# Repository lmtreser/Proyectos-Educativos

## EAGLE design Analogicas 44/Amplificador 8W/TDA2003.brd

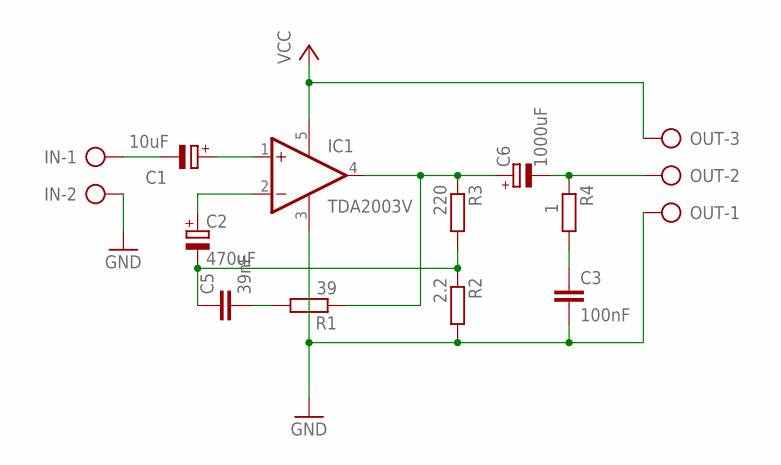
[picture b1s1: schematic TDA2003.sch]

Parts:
C1: 10uF; E2,5-6
C2: 470uF; E5-10,5
C3: 100nF; C025-025X050
C5: 39nF; C025-025X050
C6: 1000uF; E5-13
IC1: TDA2003V; CB360
IN: AK500/2-H
OUT: AK500/3-H
R1: 39; 0207/10
R2: 2.2; 0207/10
R3: 220; 0207/10
R4: 1; 0207/10

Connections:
GND: C3.2, IC1.3 (GND), IN.2, OUT.1, R2.2
unnamed: C1.+, IC1.1 (+IN)
unnamed: C1.-, IN.1
unnamed: C6.+, IC1.4 (OUT), R1.1, R3.1
unnamed: C6.-, OUT.2, R4.1
unnamed: C2.-, C5.1, R2.1, R3.2
unnamed: C3.1, R4.2
unnamed: C2.+, IC1.2 (-IN)
unnamed: C5.2, R1.2
VCC: IC1.5 (V+), OUT.3

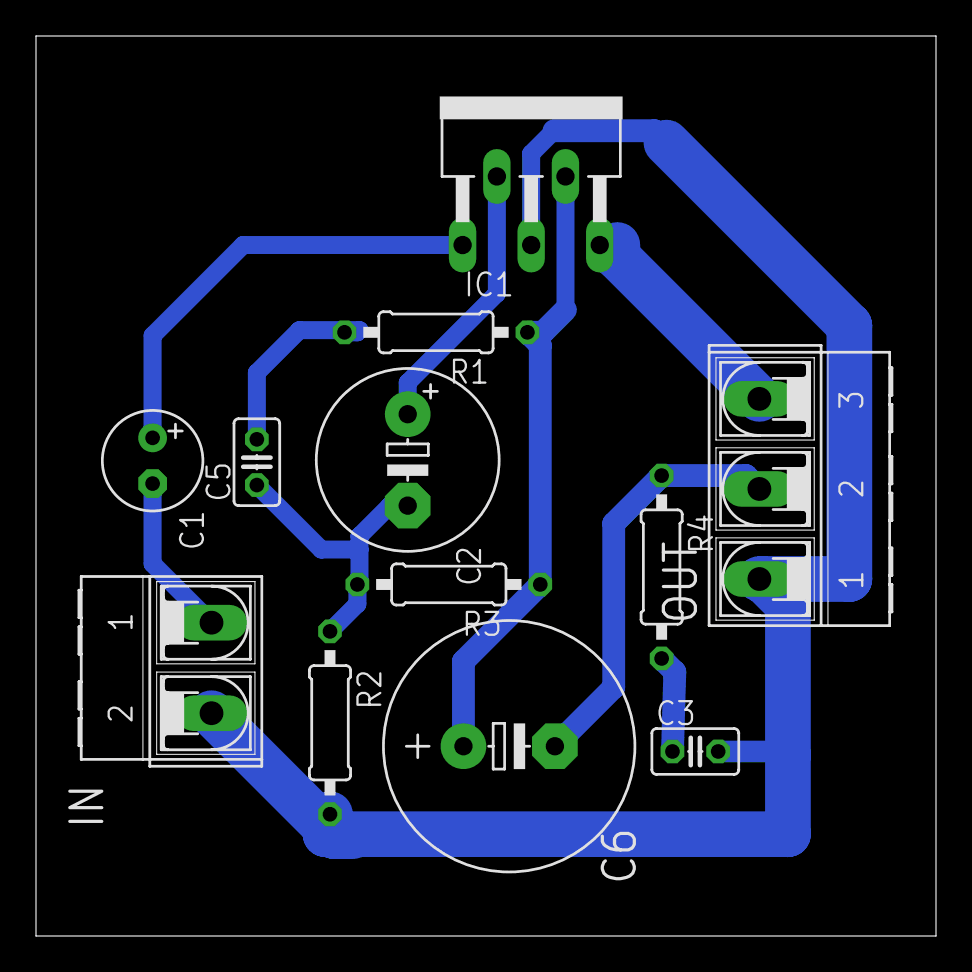
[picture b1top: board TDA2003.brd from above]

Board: 2 copper layers, 50.0 x 50.0 mm, 12 parts (0 on the bottom side), 10 nets.

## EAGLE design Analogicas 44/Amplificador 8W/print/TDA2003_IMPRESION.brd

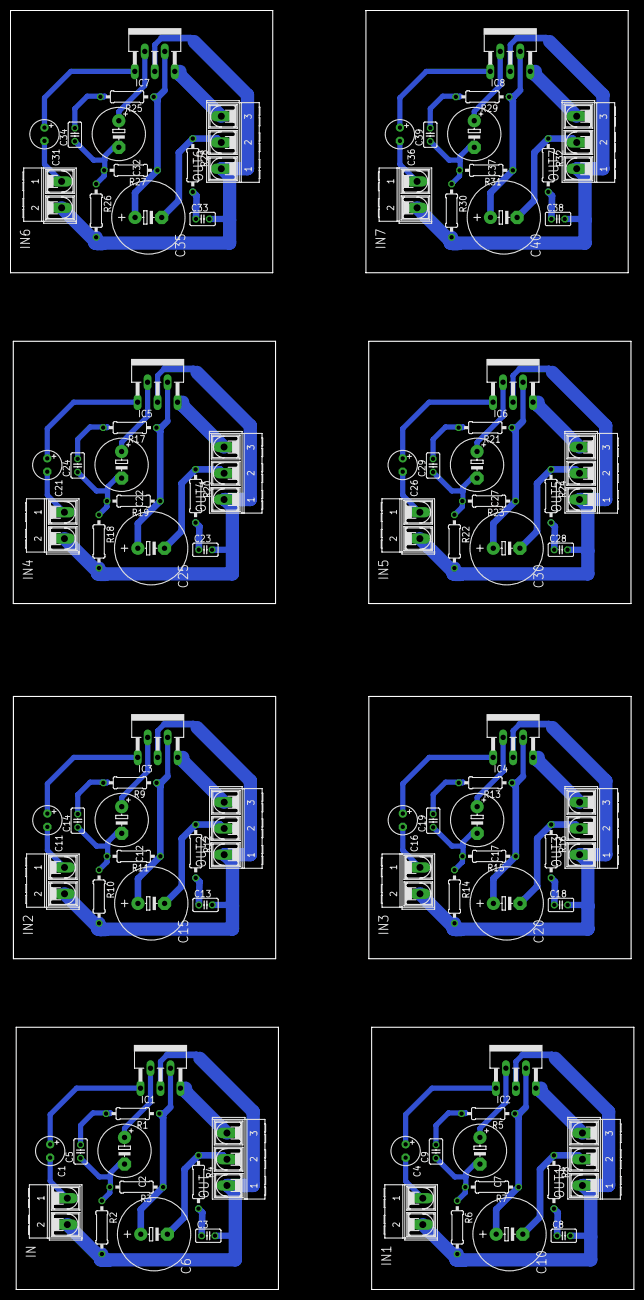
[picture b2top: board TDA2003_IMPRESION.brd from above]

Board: 2 copper layers, 118.9 x 243.9 mm, 96 parts (0 on the bottom side), 80 nets.

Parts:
C1, C4, C11, C16, C21, C26, C31, C36: 10uF; E2,5-6
C2, C7, C12, C17, C22, C27, C32, C37: 470uF; E5-10,5
C3, C8, C13, C18, C23, C28, C33, C38: 100nF; C025-025X050
C5, C9, C14, C19, C24, C29, C34, C39: 39nF; C025-025X050
C6, C10, C15, C20, C25, C30, C35, C40: 1000uF; E5-13
IC1, IC2, IC3, IC4, IC5, IC6, IC7, IC8: TDA2003V; CB360
IN, IN1, IN2, IN3, IN4, IN5, IN6, IN7: AK500/2-H
OUT, OUT1, OUT2, OUT3, OUT4, OUT5, OUT6, OUT7: AK500/3-H
R1, R5, R9, R13, R17, R21, R25, R29: 39; 0207/10
R2, R6, R10, R14, R18, R22, R26, R30: 2.2; 0207/10
R3, R7, R11, R15, R19, R23, R27, R31: 220; 0207/10
R4, R8, R12, R16, R20, R24, R28, R32: 1; 0207/10

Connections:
GND: C3.2, IC1.3, IN.2, OUT.1, R2.2
GND1: C8.2, IC2.3, IN1.2, OUT1.1, R6.2
GND2: C13.2, IC3.3, IN2.2, OUT2.1, R10.2
GND3: C18.2, IC4.3, IN3.2, OUT3.1, R14.2
GND4: C23.2, IC5.3, IN4.2, OUT4.1, R18.2
GND5: C28.2, IC6.3, IN5.2, OUT5.1, R22.2
GND6: C33.2, IC7.3, IN6.2, OUT6.1, R26.2
GND7: C38.2, IC8.3, IN7.2, OUT7.1, R30.2
unnamed: C1.+, IC1.1
unnamed: C1.-, IN.1
unnamed: C6.+, IC1.4, R1.1, R3.1
unnamed: C6.-, OUT.2, R4.1
unnamed: C2.-, C5.1, R2.1, R3.2
unnamed: C3.1, R4.2
unnamed: C2.+, IC1.2
unnamed: C5.2, R1.2
unnamed: C4.+, IC2.1
unnamed: C4.-, IN1.1
unnamed: C10.+, IC2.4, R5.1, R7.1
unnamed: C10.-, OUT1.2, R8.1
unnamed: C7.-, C9.1, R6.1, R7.2
unnamed: C8.1, R8.2
unnamed: C7.+, IC2.2
unnamed: C9.2, R5.2
unnamed: C11.+, IC3.1
unnamed: C11.-, IN2.1
unnamed: C15.+, IC3.4, R9.1, R11.1
unnamed: C15.-, OUT2.2, R12.1
unnamed: C12.-, C14.1, R10.1, R11.2
unnamed: C13.1, R12.2
unnamed: C12.+, IC3.2
unnamed: C14.2, R9.2
unnamed: C16.+, IC4.1
unnamed: C16.-, IN3.1
unnamed: C20.+, IC4.4, R13.1, R15.1
unnamed: C20.-, OUT3.2, R16.1
unnamed: C17.-, C19.1, R14.1, R15.2
unnamed: C18.1, R16.2
unnamed: C17.+, IC4.2
unnamed: C19.2, R13.2
unnamed: C21.+, IC5.1
unnamed: C21.-, IN4.1
unnamed: C25.+, IC5.4, R17.1, R19.1
unnamed: C25.-, OUT4.2, R20.1
unnamed: C22.-, C24.1, R18.1, R19.2
unnamed: C23.1, R20.2
unnamed: C22.+, IC5.2
unnamed: C24.2, R17.2
unnamed: C26.+, IC6.1
unnamed: C26.-, IN5.1
unnamed: C30.+, IC6.4, R21.1, R23.1
unnamed: C30.-, OUT5.2, R24.1
unnamed: C27.-, C29.1, R22.1, R23.2
unnamed: C28.1, R24.2
unnamed: C27.+, IC6.2
unnamed: C29.2, R21.2
unnamed: C31.+, IC7.1
unnamed: C31.-, IN6.1
unnamed: C35.+, IC7.4, R25.1, R27.1
unnamed: C35.-, OUT6.2, R28.1
unnamed: C32.-, C34.1, R26.1, R27.2
unnamed: C33.1, R28.2
unnamed: C32.+, IC7.2
unnamed: C34.2, R25.2
unnamed: C36.+, IC8.1
unnamed: C36.-, IN7.1
unnamed: C40.+, IC8.4, R29.1, R31.1
unnamed: C40.-, OUT7.2, R32.1
unnamed: C37.-, C39.1, R30.1, R31.2
unnamed: C38.1, R32.2
unnamed: C37.+, IC8.2
unnamed: C39.2, R29.2
VCC: IC1.5, OUT.3
VCC1: IC2.5, OUT1.3
VCC2: IC3.5, OUT2.3
VCC3: IC4.5, OUT3.3
VCC4: IC5.5, OUT4.3
VCC5: IC6.5, OUT5.3
VCC6: IC7.5, OUT6.3
VCC7: IC8.5, OUT7.3

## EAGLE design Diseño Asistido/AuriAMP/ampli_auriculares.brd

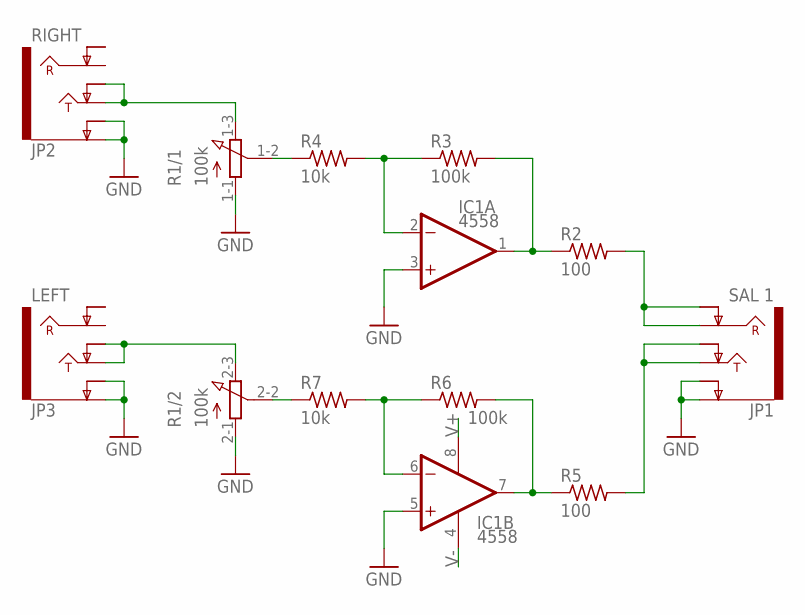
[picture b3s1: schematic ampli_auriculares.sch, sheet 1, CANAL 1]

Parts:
IC1: 4558; DIL08
JP1: SAL 1; AUDIO-JACK-.25-INCH-HORIZ-PTH
JP2: RIGHT; AUDIO-JACK-.25-INCH-HORIZ-PTH
JP3: LEFT; AUDIO-JACK-.25-INCH-HORIZ-PTH
R1: 100k; 3RP/1610G
R2, R5: 100; 0204/7
R3, R6: 100k; 0204/7
R4, R7: 10k; 0204/7

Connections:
GND: IC1.3 (+IN), IC1.5 (+IN), JP1.SLEEVE (EARTH), JP1.SLEEVE-NORM (EARTH-NORM), JP2.SLEEVE (EARTH), JP2.SLEEVE-NORM (EARTH-NORM), JP3.SLEEVE (EARTH), JP3.SLEEVE-NORM (EARTH-NORM), R1.1-1 (A), R1.2-1 (A); also elsewhere on the board
unnamed: IC1.1 (OUT), R2.1, R3.2
unnamed: JP2.TIP, JP2.TIP-NORM, R1.1-3 (E)
unnamed: IC1.2 (-IN), R3.1, R4.2
unnamed: IC1.7 (OUT), R5.1, R6.2
unnamed: IC1.6 (-IN), R6.1, R7.2
unnamed: R1.1-2 (S), R4.1
unnamed: R1.2-2 (S), R7.1
unnamed: JP1.RING, JP1.RING-NORM, R2.2
unnamed: JP1.TIP, JP1.TIP-NORM, R5.2
unnamed: JP3.TIP, JP3.TIP-NORM, R1.2-3 (E)
V+: IC1.8 (V+); also elsewhere on the board
V-: IC1.4 (V-); also elsewhere on the board

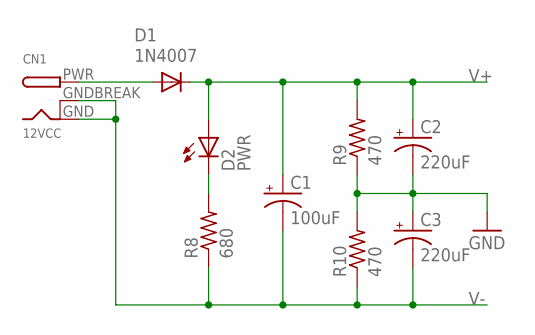
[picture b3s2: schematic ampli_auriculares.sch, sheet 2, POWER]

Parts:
C1: 100uF; E2,5-6
C2, C3: 220uF; E2,5-6
CN1: 12VCC; DCJACK_2MM_PTH
D1: 1N4007; DO41-10
D2: PWR; LED3MM
R8: 680; 0204/7
R9, R10: 470; 0207/10

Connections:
GND: C2.-, C3.+, R9.1, R10.2; also elsewhere on the board
unnamed: CN1.PWR, D1.A
unnamed: D2.K (C), R8.2
V+: C1.+, C2.+, D1.C, D2.A, R9.2; also elsewhere on the board
V-: C1.-, C3.-, CN1.GND, CN1.GNDBREAK, R8.1, R10.1; also elsewhere on the board

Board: 2 copper layers, 20 parts (0 on the bottom side), 15 nets, no tracks yet.

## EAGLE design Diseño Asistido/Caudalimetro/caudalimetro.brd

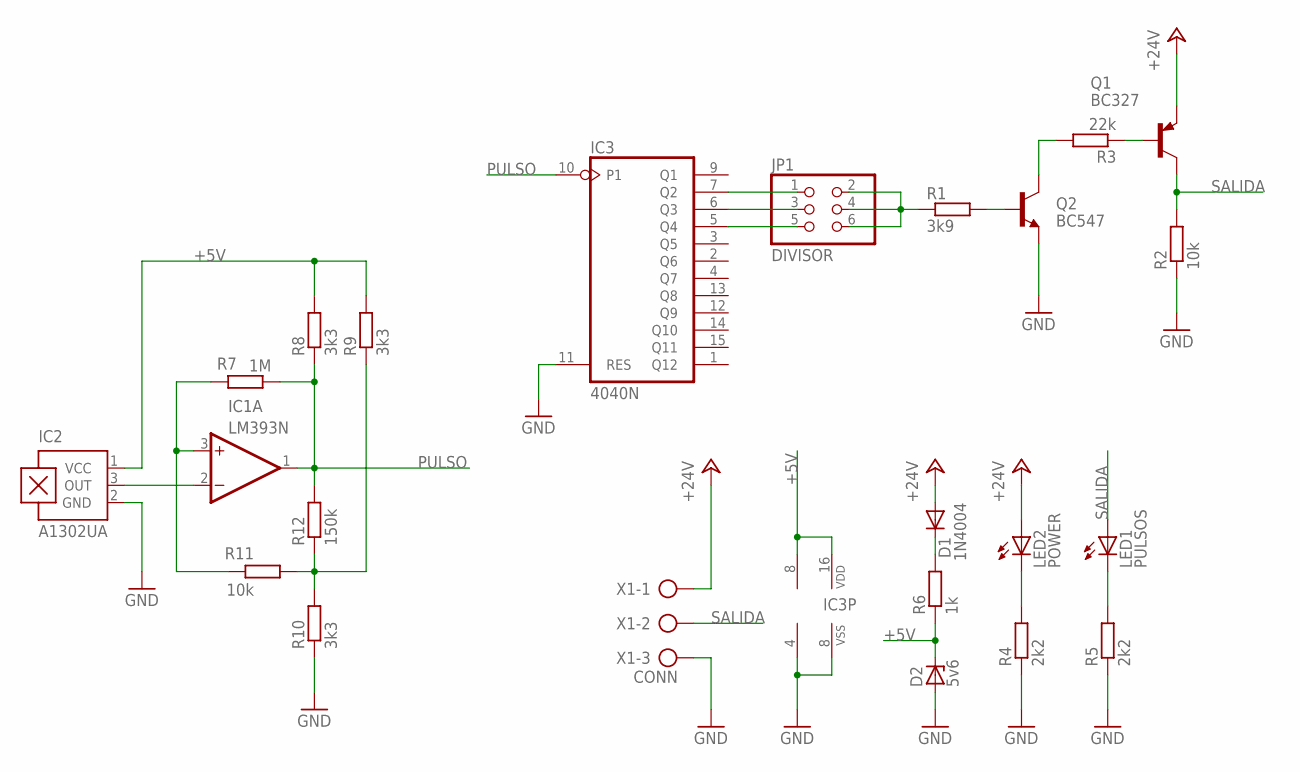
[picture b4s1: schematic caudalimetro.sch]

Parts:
D1: 1N4004; DO41-10
D2: 5v6; ZDIO-2.5
IC1: LM393N; DIL08
IC2: A1302UA; SIP3-UA
IC3: 4040N; DIL16
JP1: DIVISOR; 2X03
LED1: PULSOS; LED3MM
LED2: POWER; LED3MM
Q1: BC327; TO92
Q2: BC547; TO92
R1: 3k9; 0207/2V
R2, R11: 10k; 0207/2V
R3: 22k; 0207/2V
R4, R5: 2k2; 0207/2V
R6: 1k; 0207/2V
R7: 1M; 0207/2V
R8, R9, R10: 3k3; 0207/2V
R12: 150k; 0207/2V
X1: CONN; AK300/3

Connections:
+5V: D2.C, IC1.8 (V+), IC2.1 (VCC), IC3.16 (VDD), R6.1, R8.2, R9.2
+24V: D1.A, LED2.A, Q1.1 (E), X1.1
GND: D2.A, IC1.4 (V-), IC2.2 (GND), IC3.8 (VSS), IC3.11 (RES), Q2.1 (E), R2.1, R4.1, R5.1, R10.1, X1.3
unnamed: IC3.7 (Q2), JP1.1
unnamed: IC3.6 (Q3), JP1.3
unnamed: IC3.5 (Q4), JP1.5
unnamed: Q2.2 (B), R1.2
unnamed: Q2.3 (C), R3.2
unnamed: LED2.K (C), R4.2
unnamed: LED1.K (C), R5.2
unnamed: IC1.2 (-IN), IC2.3 (OUT)
unnamed: D1.C, R6.2
unnamed: JP1.2, JP1.4, JP1.6, R1.1
unnamed: Q1.2 (B), R3.1
unnamed: R9.1, R10.2, R11.1, R12.1
unnamed: IC1.3 (+IN), R7.2, R11.2
PULSO: IC1.1 (OUT), IC3.10 (P1), R7.1, R8.1, R12.2
SALIDA: LED1.A, Q1.3 (C), R2.2, X1.2

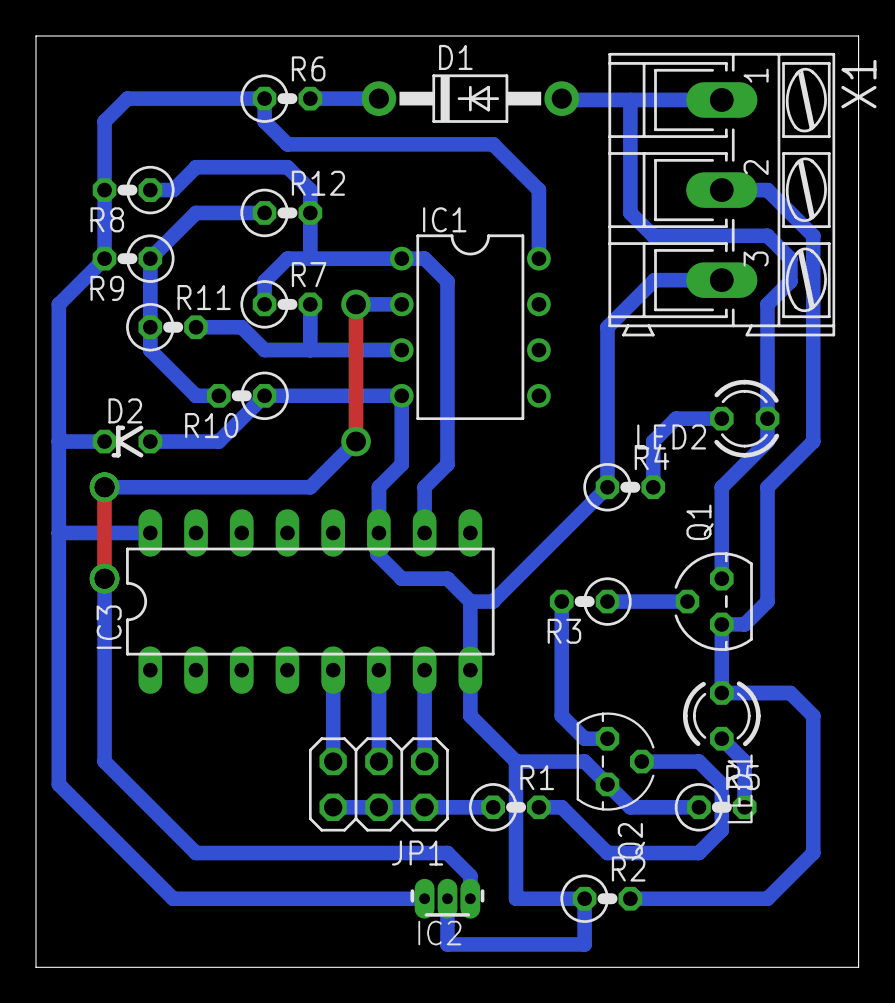
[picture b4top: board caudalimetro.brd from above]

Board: 2 copper layers, 45.7 x 51.7 mm, 23 parts (0 on the bottom side), 18 nets.

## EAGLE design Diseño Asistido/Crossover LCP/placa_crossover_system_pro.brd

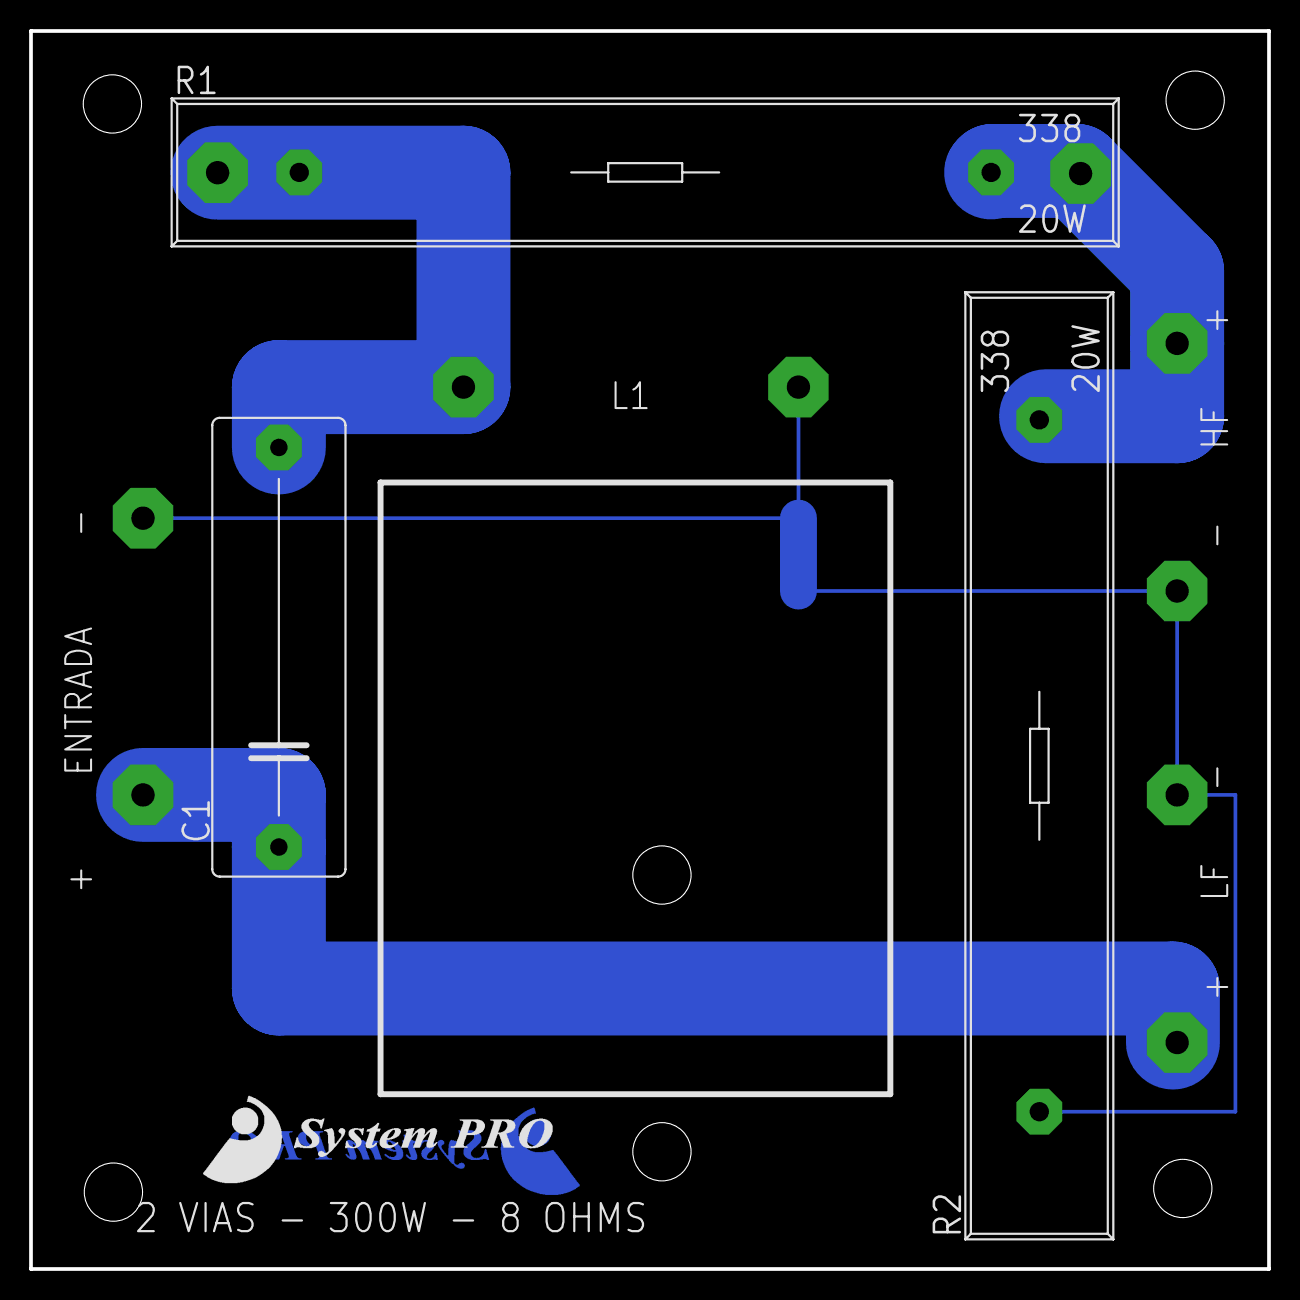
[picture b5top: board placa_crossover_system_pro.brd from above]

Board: 2 copper layers, 85.0 x 85.0 mm, 13 parts (0 on the bottom side), 4 nets.

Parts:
C1: 2,2uF; C27.5B9
E$1, E$2, E$3, E$4, E$5, E$6, E$7, E$8, E$9, E$10: 4,16O1,6
R1, R2: 10; KWP338

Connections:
GND: E$2.1, E$6.1, E$8.1, E$9.1, R2.1
S$1: C1.2, E$3.1, E$5.1, R1.1
S$2: E$7.1, R1.2, R2.2
S$3: C1.1, E$4.1, E$10.1

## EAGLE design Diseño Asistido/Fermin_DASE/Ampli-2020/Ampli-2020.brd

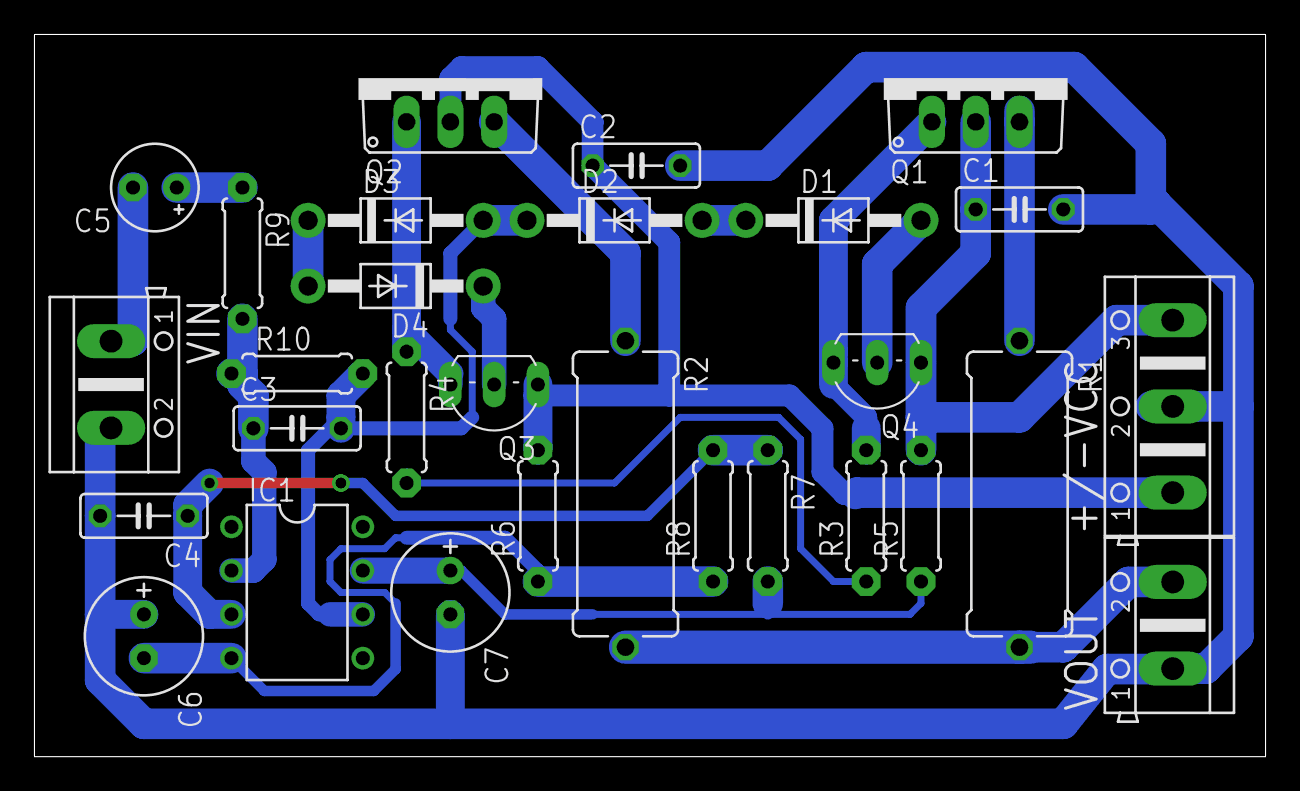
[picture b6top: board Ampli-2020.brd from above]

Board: 2 copper layers, 71.4 x 41.9 mm, 29 parts (0 on the bottom side), 20 nets.

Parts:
+/-VCC: AK500/3
C1, C2, C3, C4: C050-025X075
C5: E2,5-5
C6, C7: E2,5-7
D1, D2, D3, D4: 1N4004; DO41-10
IC1: TL071P; DIL08
Q1: TIP41C; TO220AV
Q2: TIP42C; TO220AV
Q3: BC560; TO92-EBC
Q4: BC550C; TO92-EBC
R1, R2: 0617/17
R3, R4, R5, R6, R7, R8, R9, R10: 0207/7
VIN: AK500/2
VOUT: AK500/2

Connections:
GND: +/-VCC.2, C1.2, C2.2, C4.2, C6.+, C7.-, VIN.2, VOUT.1
unnamed: Q2.B, Q3.E, R4.1
unnamed: D1.C, D2.A
unnamed: C3.2, D2.C, D3.A, IC1.6, R10.2
unnamed: D3.C, D4.A
unnamed: D1.A, Q4.B
unnamed: Q1.B, Q4.E, R3.2
unnamed: R3.1, R4.2
unnamed: D4.C, Q3.B
unnamed: Q2.E, R2.1
unnamed: Q1.E, R1.1
unnamed: R1.2, R2.2, VOUT.2
unnamed: C5.+, R9.1
unnamed: +/-VCC.1, C2.1, Q2.C, Q3.C, R6.2
unnamed: C5.-, VIN.1
unnamed: +/-VCC.3, C1.1, Q1.C, Q4.C, R5.2
unnamed: C7.+, IC1.7, R5.1, R7.2
unnamed: C3.1, IC1.2, R9.2, R10.1
unnamed: C4.1, IC1.3, R7.1, R8.2
V2: C6.-, IC1.4, R6.1, R8.1

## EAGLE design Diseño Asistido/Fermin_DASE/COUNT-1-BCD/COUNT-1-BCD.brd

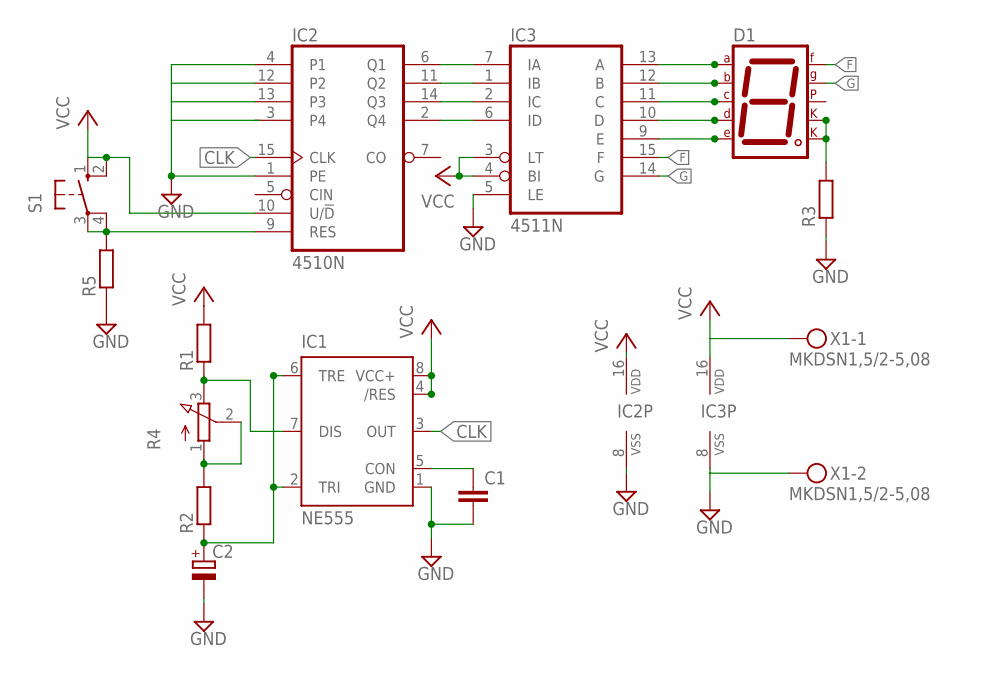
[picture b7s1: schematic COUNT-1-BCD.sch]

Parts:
C1: C2.5/2; C2.5-2
C2: CPOL-EUE2,5-6E; E2,5-6E
D1: 7SEG-CK; 7SEG-13
IC1: NE555; DIL-08
IC2: 4510N; DIL16
IC3: 4511N; DIL16
R1, R2, R3, R5: R-EU_0204/7; 0204/7
R4: 3RP/1610N
S1: 10-XX; B3F-10XX
X1: MKDSN1,5/2-5,08

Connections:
CLK: IC1.3 (OUT), IC2.15 (CLK)
F: D1.9 (F), IC3.15 (F)
G: D1.10 (G), IC3.14 (G)
GND: C1.2, C2.-, IC1.1 (GND), IC2.1 (PE), IC2.4 (P1), IC2.8 (VSS), IC2.12 (P2), IC2.13 (P3), IC3.5 (LE), IC3.8 (VSS), R3.1, R5.1, X1.2
unnamed: D1.3 (CK1), D1.8 (CK2), R3.2
unnamed: D1.7 (A), IC3.13 (A)
unnamed: D1.6 (B), IC3.12 (B)
unnamed: D1.4 (C), IC3.11 (C)
unnamed: D1.2 (D), IC3.10 (D)
unnamed: D1.1 (E), IC3.9 (E)
unnamed: C1.1, IC1.5 (CON)
unnamed: C2.+, IC1.2 (TRI), IC1.6 (TRE), R2.1
unnamed: IC2.11 (Q2), IC3.1 (IB)
unnamed: IC2.14 (Q3), IC3.2 (IC)
unnamed: IC2.9 (RES), R5.2, S1.3, S1.4 (P1)
unnamed: IC2.2 (Q4), IC3.6 (ID)
unnamed: IC2.6 (Q1), IC3.7 (IA)
unnamed: IC1.7 (DIS), R1.1, R4.3 (E)
unnamed: R2.2, R4.1 (A), R4.2 (S)
VCC: IC1.4 (/RES), IC1.8 (VCC+), IC2.10 (U/!D), IC2.16 (VDD), IC3.3 (LT), IC3.4 (BI), IC3.16 (VDD), R1.2, S1.1 (S), S1.2 (S1), X1.1

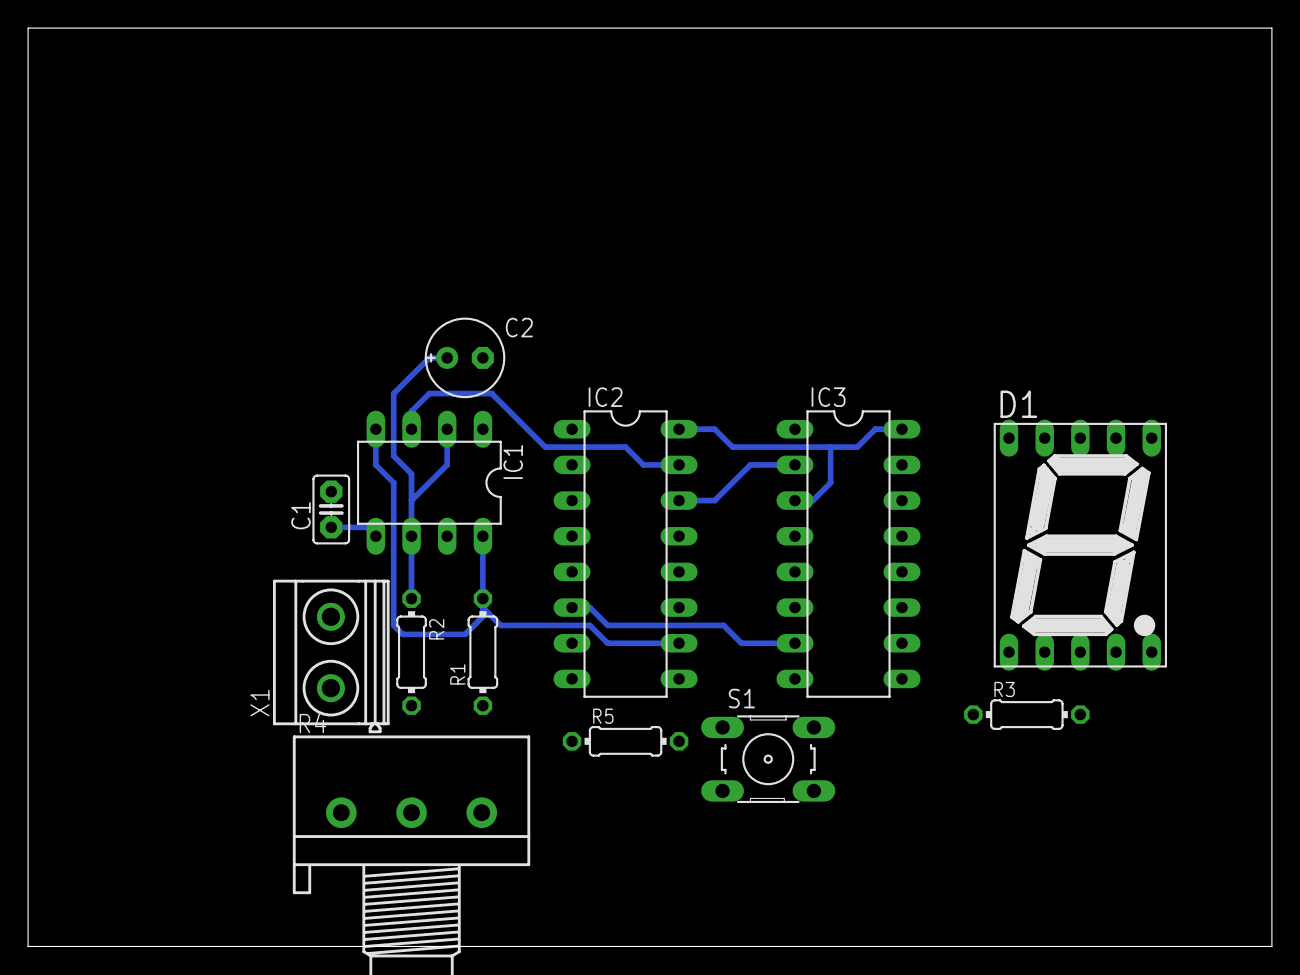
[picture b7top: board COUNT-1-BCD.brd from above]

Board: 2 copper layers, 88.6 x 65.4 mm, 13 parts (0 on the bottom side), 20 nets.

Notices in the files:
parts and their libraries:
SparkFun-Connectors: Licensing: Creative Commons ShareAlike 4.0 International - https://creativecommons.org/licenses/by-sa/4.0
